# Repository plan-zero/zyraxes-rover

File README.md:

# Zyraxes Rover 

This is a platform that will be used for educational purposes and/or other projects.
This is inspired by the existing [JPL’s rover](https://github.com/nasa-jpl/open-source-rover).

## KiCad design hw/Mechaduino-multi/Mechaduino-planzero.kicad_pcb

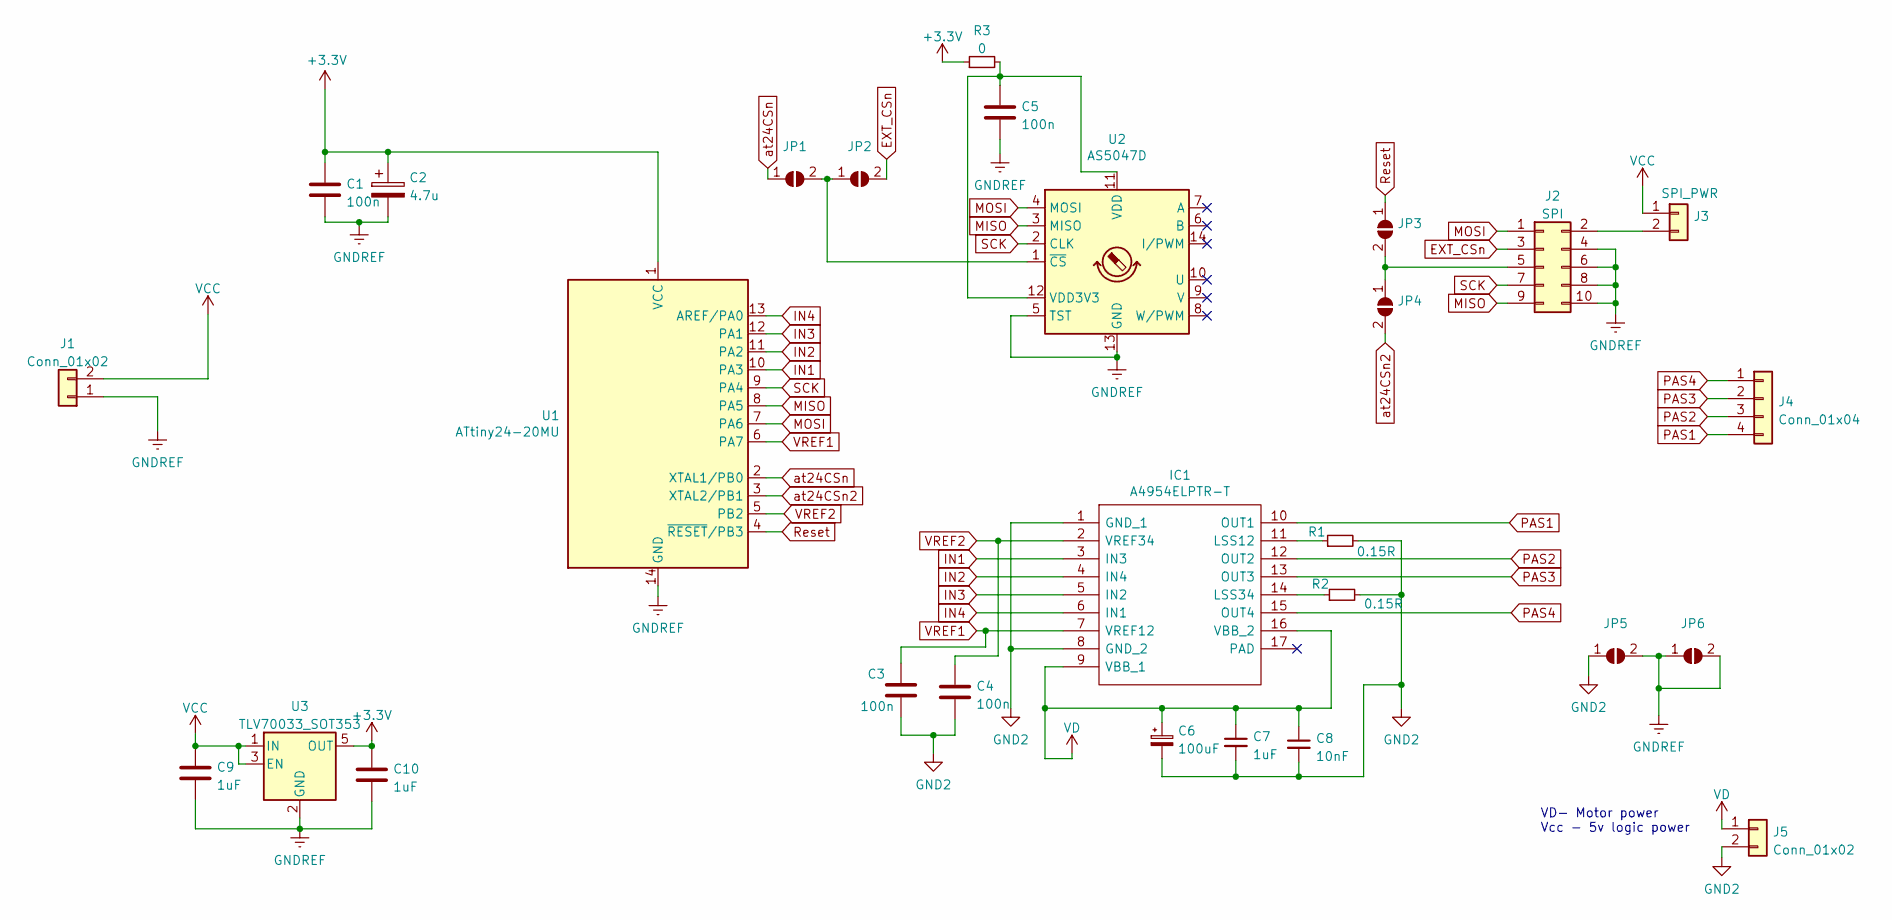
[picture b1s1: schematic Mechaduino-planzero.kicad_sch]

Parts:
C1, C3, C4, C5: 100n; C_0805_2012Metric_Pad1.18x1.45mm_HandSolder
C2: 4.7u; C_0805_2012Metric_Pad1.18x1.45mm_HandSolder
C6: 100uF; CP_Elec_8x10
C7, C9, C10: 1uF; C_0805_2012Metric_Pad1.18x1.45mm_HandSolder
C8: 10nF; C_0603_1608Metric_Pad1.08x0.95mm_HandSolder
IC1: A4954ELPTR-T; TSSOP-16-1EP_4.4x5mm_P0.65mm_EP3x3mm; Manufacturer_Part_Number A4954ELPTR-T
J1: Conn_01x02; PinSocket_1x02_P2.54mm_Horizontal
J2: SPI; IDC-Header_2x05_P2.54mm_Vertical
J3: SPI_PWR; PinSocket_1x02_P2.54mm_Vertical
J4: Conn_01x04; PinSocket_1x04_P2.54mm_Horizontal
J5: Conn_01x02; TerminalBlock_bornier-2_P5.08mm
JP1, JP2, JP3, JP4, JP5, JP6: SolderJumper-2_P1.3mm_Open_Pad1.0x1.5mm
R1, R2: 0.15R; R_0805_2012Metric_Pad1.20x1.40mm_HandSolder
R3: 0; R_0805_2012Metric_Pad1.20x1.40mm_HandSolder
U1: ATtiny24-20MU; SOIC-14_3.9x8.7mm_P1.27mm
U2: AS5047D; TSSOP-14_4.4x5mm_P0.65mm
U3: TLV70033_SOT353; SOT-353_SC-70-5

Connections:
+3V3: C1.1, C2.1, C10.1, R3.1, U1.1 (VCC), U3.5 (OUT)
EXT_CSn: J2.3, JP2.2 (B)
GND2: C3.2, C4.2, C6.2, C7.2, C8.2, IC1.1 (GND_1), IC1.8 (GND_2), J5.2, JP5.1 (A), R1.2, R2.2
GNDREF: C1.2, C2.2, C5.2, C9.2, C10.2, J1.1, J2.4, J2.6, J2.8, J2.10, JP5.2 (B), JP6.1 (A), JP6.2 (B), U1.14 (GND), U2.5 (TST), U2.13 (GND), U3.2 (GND)
IN1: IC1.3 (IN3), U1.10 (PA3)
IN2: IC1.4 (IN4), U1.11 (PA2)
IN3: IC1.5 (IN2), U1.12 (PA1)
IN4: IC1.6 (IN1), U1.13 (AREF/PA0)
MISO: J2.9, U1.8 (PA5), U2.3 (MISO)
MOSI: J2.1, U1.7 (PA6), U2.4 (MOSI)
unnamed: C5.1, R3.2, U2.11 (VDD), U2.12 (VDD3V3)
unnamed: IC1.11 (LSS12), R1.1
unnamed: IC1.14 (LSS34), R2.1
unnamed: J2.2, J3.2
unnamed: J2.5, JP3.2 (B), JP4.1 (A)
unnamed: JP1.2 (B), JP2.1 (A), U2.1 (~CS)
PAS1: IC1.10 (OUT1), J4.4
PAS2: IC1.12 (OUT2), J4.3
PAS3: IC1.13 (OUT3), J4.2
PAS4: IC1.15 (OUT4), J4.1
VCC: C9.1, J1.2, J3.1, U3.1 (IN), U3.3 (EN)
VD: C6.1, C7.1, C8.1, IC1.9 (VBB_1), IC1.16 (VBB_2), J5.1
VREF1: C3.1, IC1.7 (VREF12), U1.6 (PA7)
VREF2: C4.1, IC1.2 (VREF34), U1.5 (PB2)
at24CSn: JP1.1 (A), U1.2 (XTAL1/PB0)
at24CSn2: JP4.2 (B), U1.3 (XTAL2/PB1)

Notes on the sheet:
VD- Motor power Vcc - 5v logic power

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
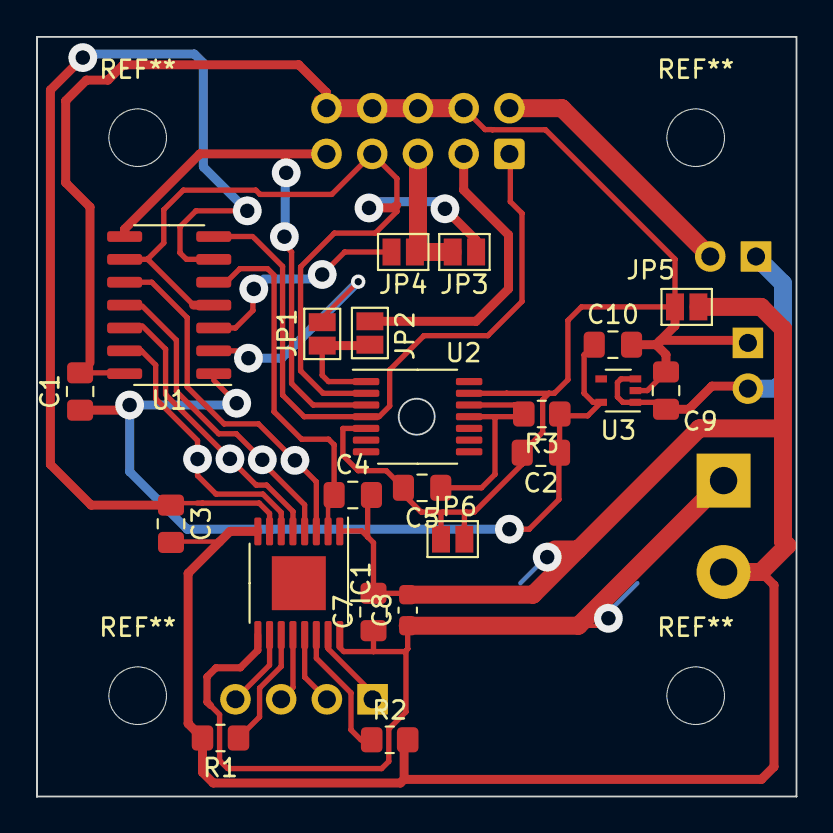
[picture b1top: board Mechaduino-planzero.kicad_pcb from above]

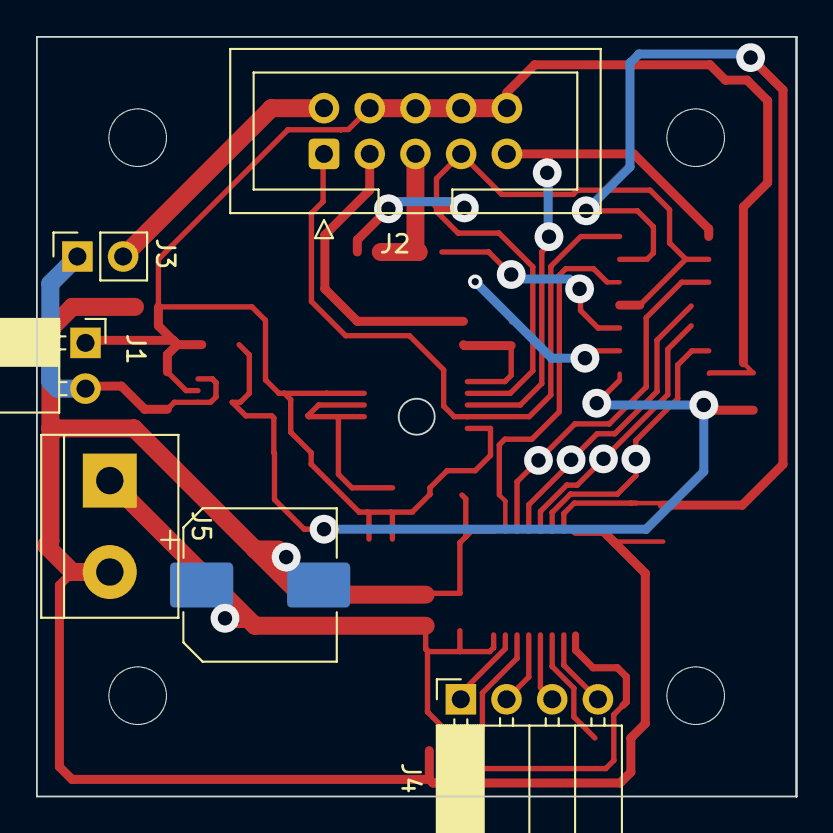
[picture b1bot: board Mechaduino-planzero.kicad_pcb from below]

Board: 2 copper layers, 42.2 x 42.2 mm, 28 parts (6 on the bottom side), 27 nets.

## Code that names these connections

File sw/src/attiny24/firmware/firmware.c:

/* Test application for the SPI-via-USI-driver. */

#include "spi_driver.h"
#include "sin_lut_microstep_16.h"
#include <avr/interrupt.h>

#define F_CPU 8000000UL
#include <util/delay.h>


#define FIRMWARE_VERSION 0x10

#define SPIMODE 0	// Sample on leading _rising_ edge, setup on trailing _falling_ edge.

#define RPM_CONST 18750


#define IN1	PA0
#define IN2 PA1
#define IN3 PA2
#define IN4 PA3

#define INPORT PORTA


//const float iMAX = 1.0;
//const float rSense = 0.150;
//volatile int uMAX = (255/3.3)*(iMAX*10*rSense);

//this if for 1.5A
#define EFFORT_DEFAULT 37
#define EFFORT_MAX	   173

uint8_t EFFORT = EFFORT_DEFAULT;


static inline void step(int8_t dir)
{
  int16_t v_coil_A = 0, v_coil_B = 0, angle_A = 0, angle_B = 0;
  static uint16_t pos_a = 0, pos_b = POS_OFFSET;


  angle_A = (int8_t)pgm_read_byte(&sin_lut[pos_a % SIN_LUT_LEN]);
  pos_a += dir;
  angle_B = (int8_t)pgm_read_byte(&sin_lut[pos_b % SIN_LUT_LEN]);
  pos_b += dir;

  v_coil_A = ( angle_A* EFFORT )/128;
  v_coil_B = ( angle_B* EFFORT )/128;

  OCR0B = abs(v_coil_A);
  OCR0A = abs(v_coil_B);

  INPORT &= 0xF0;
  if (v_coil_A >= 0)  {
    INPORT |= _BV(IN2);
    INPORT &= ~_BV(IN1);
  }
  else {
    INPORT &= ~_BV(IN2);
    INPORT |= _BV(IN1);
  }

  if (v_coil_B >= 0) {
    INPORT |= _BV(IN4);
    INPORT &= ~_BV(IN3);
  }
  else {
    INPORT &= ~_BV(IN4);
    INPORT |= _BV(IN3);
  }
}

#define TIMER_INTERVAL_US 100
#define TIMER_CONSTANT	(F_CPU / 8 / 1000000)

void timer_init() {
    // Set CTC mode with OCR1A as top value
    TCCR1B |= (1 << WGM12);
    
    // Set prescaler to 8
    TCCR1B |= (1 << CS11);
    
    // Set compare match value for 100us
    OCR1A = TIMER_CONSTANT * TIMER_INTERVAL_US;

	// Reset timer count reg to zero
	TCNT1 = 0;

	//Configure PWM for motor control
    TCCR0A |= _BV(COM0B1) | _BV(COM0A1) | _BV(WGM01) | _BV(WGM00);
    TCCR0B |= _BV(CS00);
	DDRB |= _BV(PB2);
	DDRA |= _BV(PA7);
    OCR0A = 0;
    OCR0B = 0;

	
}

static inline void start_timer(uint16_t cmp_match)
{
	OCR1A = TIMER_CONSTANT * cmp_match;
	TCNT1 = 0;
	TIMSK1 |= (1 << OCIE1A);
}

static inline void stop_timer()
{
	TIMSK1 &= ~(1 << OCIE1A);
}

volatile char timer_triggered = 0;
ISR(TIM1_COMPA_vect) {
	timer_triggered = 1;
}



int main()
{

	
	timer_init();
	spiX_initslave(SPIMODE);	// Init SPI driver as slave.
	sei();		// Must do this to make driver work.


	//Configure IN1-4 as output
	DDRA |= _BV(IN1) | _BV(IN2) | _BV(IN3) | _BV(IN4);
	DDRB |= 1 << PB0;
	PORTB |= 1 << PB0;
	
	uint16_t steps_to_do = 0;
	uint8_t task = 0;
	int8_t dir = 0;
	uint8_t master_cmd = 0;
	uint16_t rpm_to_us = 0;
	uint8_t effort_to_set = 0;
	uint8_t checksum = 0;

	spiX_put(SlaveSYNC);

	do {

		if(timer_triggered)
		{
			PORTB &= ~(1 << PB0);
			if(steps_to_do)
			{
				step(dir);
				//if this is free running
				if(steps_to_do != 0x1fff)
					steps_to_do--;
			}
			else
			{
				stop_timer();
				PORTB |= (1 << PB0);
			}
			timer_triggered = 0;
			PORTB |= (1 << PB0);
		}

		if(spiX_status.doChecksum)
		{
			
			master_cmd = spi_received_data[0] >> 6;
			calculated_checksum = spi_received_data[0] + spi_received_data[1] + spi_received_data[2];

			if(master_cmd == MasterSYNC)
			{
				spiX_put(SlaveSYNC);
			}
			else if (master_cmd == MasterSTEP)
			{
				spiX_put(SlaveSTEP);
			}
			else if (master_cmd == MasterSETUP)
			{
				spiX_put(SlaveSETUP);
			}
			spiX_status.doChecksum = 0;
		}
		else if(spiX_status.transferComplete)
		{

			master_cmd = spi_received_data[0] >> 6;
			checksum = spi_received_data[3];

			if(checksum == calculated_checksum)
			{

				if(master_cmd == MasterSTEP)
				{
					
					steps_to_do = ((spi_received_data[0] & 0x1f) << 8) | spi_received_data[1];
					if( (spi_received_data[0] >> 5) & 0x1)
						dir = 1;
					else
						dir = -1;
					
					rpm_to_us = RPM_CONST / (uint16_t) spi_received_data[2];
					if(rpm_to_us < TIMER_INTERVAL_US)
						rpm_to_us = TIMER_INTERVAL_US;
					start_timer(rpm_to_us);
					
				}
				else if(master_cmd == MasterSETUP)
				{
					effort_to_set = (uint8_t)spi_received_data[1];
					if(effort_to_set > EFFORT_MAX)
						effort_to_set = EFFORT_MAX;
					EFFORT = effort_to_set;
					if(spi_received_data[2] == 0xFA)
					{
						//turn off motors
						INPORT &= 0xF0;
					}

				}
			}

			spiX_status.transferComplete = 0;
			checksum = 0;
			calculated_checksum = 0;
			
		}
		
		
		
	} while(1);			// Loop forever...
}

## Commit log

2022-10-02 Initial README
2022-10-02 Add schematic for power board
2022-10-16 Add initial sch & libs for mechaduino multi
2022-10-22 update schematic
2022-10-22 update pcb layout
2022-10-26 Some updates
2022-10-27 Add new updates to driver sch / layout
2022-10-27 Remove unused kicad files
2022-10-28 First prototype
2022-10-29 AD PCB files
2023-11-26 Add schematic v0.0.4
2024-01-09 [SW] Add initial SAM4L/SAMD21 board code - ASF
2024-01-09 [SW] Add dev tools for avr
2024-01-09 [SW] Add SPI driver for attiny24; add examples for SPI and stepepr
2024-01-09 [SW] Add SAM4L blinky example
2024-01-09 [SW] Add spi example for SAM4L
2024-01-09 [SW] Fix blinky example
2024-01-09 [SW] Add flash tool wrapper for sam4L
2024-01-11 [SW] Add CS functionality as SW for USI
2024-01-11 [SW] Add 4MHZ SPI config
2024-01-13 [SW] Add exampel for AS5047D
2024-01-13 [SW] Lower BS/BCT delays
2024-01-14 [SW] Add initial zyraxes app/firmware version
2024-01-14 [SW] Fix ASF include paths
2024-01-14 [SW] Add support for Fixed PCS selection
2024-01-15 [SW] Enable decmode SPI
2024-01-15 [SW] Add NPCS3 as SPI CS
2024-01-22 [SW] Add gitignore for app
2024-01-22 [SW] Attiny24 firmware first version
2024-01-22 [SW] Fix encoder read for 8bits
2024-01-25 [SW] Disable/enable MOSI pin from t24 between SPI transfers
2024-01-25 [SW] Increase CS-SCK delay
2024-01-25 [SW] Remove duplicated file
2024-01-25 [SW] Add PWM control via SPI
2024-01-25 [SW] Add motor control - working version
2024-01-26 [SW] Move constants to different C file
2024-01-26 [SW] Add initial nvm code
2024-02-04 [SW] Change SPI driver CS to PB0
2024-02-04 [SW] Add 1/32 step as motor example using sin
2024-02-13 [HW] Add schematic for v1.0.0
2024-03-31 [SW] Add support for 64 microstep + scripts to generate LUT
2024-04-01 [SW] change optimization to O3
2024-04-01 [SW] Use new method for motor driver
2024-04-01 [SW] Improve stepping speed
2024-04-01 [SW] Add calibration routine - mechaduino version
2024-04-01 [SW] Add angle read form magnetic senzor routine
2024-04-01 [SW] Add method to reduce encoder resolution to save flash memory
2024-04-02 [SW] Add timmer interrupt handler at 6.5kHZ
2024-04-03 [SW] Improve motor control by doing multiple steps as once
2024-04-09 [SW] Add checkpoint code - improves in stepper demo
2024-04-09 [SW] Update gitignore
2024-04-09 [SW] Add micro64 config for firmware
2024-04-09 [SW] Add this as backup for old zyraxes firmware - it will change
2024-04-09 [SW] Add code checkpoint
2024-04-09 [SW] Add manual speed control for testing
2024-04-10 [SW] Move firmware code to another folder
2024-04-10 [SW] Add checkpoint - working version
2024-04-10 [SW] Reset page number after calibration
2024-04-10 [SW] change motor dir for calibration
2024-04-11 [SW] Add motor status
2024-04-11 [SW] Add other PCs for motors/sensor
2024-04-12 [SW] Switching to SW CS which allows broadcasting on motors
2024-04-12 [SW] Add progress for motor loop control
2024-04-14 [SW] Add progress
2024-04-15 [SW] Add new firmware for t24
2024-04-16 [SW] Add working version
2024-04-16 [SW] Fix rot variable
2024-04-20 [SW] Add init to zero position
2024-05-12 [SW] Add progress for zyraxes firmware
2024-05-14 [SW] Add remote control working version
2024-06-06 [SW] Add joystick c code for RPI
2024-06-06 [SW] Add checksum for t24 firmware
2024-06-06 [SW] Add retry cmd for motors
2024-06-06 [SW] Fix motor sync routine
2024-06-06 [SW] Change SPI config
2024-06-10 [SW] Add firmware changes for t24
2024-06-10 [SW] Add working version (branch candidate)
2024-06-12 [SW] Add abs angle for dir motors
2024-06-12 [SW] Add motor dir control test1
2024-06-13 [SW] Add work checkpoint - 2
2024-06-13 [SW] Working version - remote controller - RC
2024-06-19 [SW] Add motor stop command in firmware; fix bugs
2024-06-19 [SW] Add differential speed for turning
2024-11-07 [SW] Add current progress
2025-02-25 Add schematic file for motor driver v4.2
2025-02-25 Add schematic for zyraxes motor driver v3.5
2025-03-17 [SW] Add stepper demo for attiny24 v2 board
2025-03-17 [SW] Add initial stepper demo for atmega328p
2025-03-18 [SW] Add first working TWI example sam4l-atmega328p
2025-03-18 [SW] Increase twi speed up to 400kbs
2025-03-18 [SW] Add firmware for m328p - progress
2025-03-20 [SW] Add motor control for m328p firmware
2025-03-21 [SW] Add first SPI example atmega-magnetic sensor - working version
2025-03-21 [SW] Fix startup comunication error of magnetic sensor
2025-03-21 [SW] Fix rx/tx byte problem
2025-03-21 [SW] Add progress -1
2025-03-21 [SW] Add mangetic sensor readings
2025-03-21 [SW] Add few fixes for motor spi comm
2025-03-21 [SW] Add progress -2
2025-03-21 [SW] Add basic commands for the motor
2025-03-27 [SW] Add support for e2p firmware version and slave TWI address
2025-03-27 [SW] Add testing routines for TWI cmd/address range
2025-03-27 [SW] Refactoring the sam4l firmware
2025-03-28 [SW] Refactoring: split motor functions in two categories, SPI and TWI
2025-03-28 [SW] Refactoring: add implementation for TWI motor driver
2025-03-31 [SW] Add end switch feature for v2 atmega328p
2025-05-15 [SW] Add working version - using driver v4.2
2025-05-31 [sw] Update
2025-06-09 [SW][m328p 1.1.0] Add endswitch and release method~
2025-06-09 [SW] Fix cmd bug when force stop
